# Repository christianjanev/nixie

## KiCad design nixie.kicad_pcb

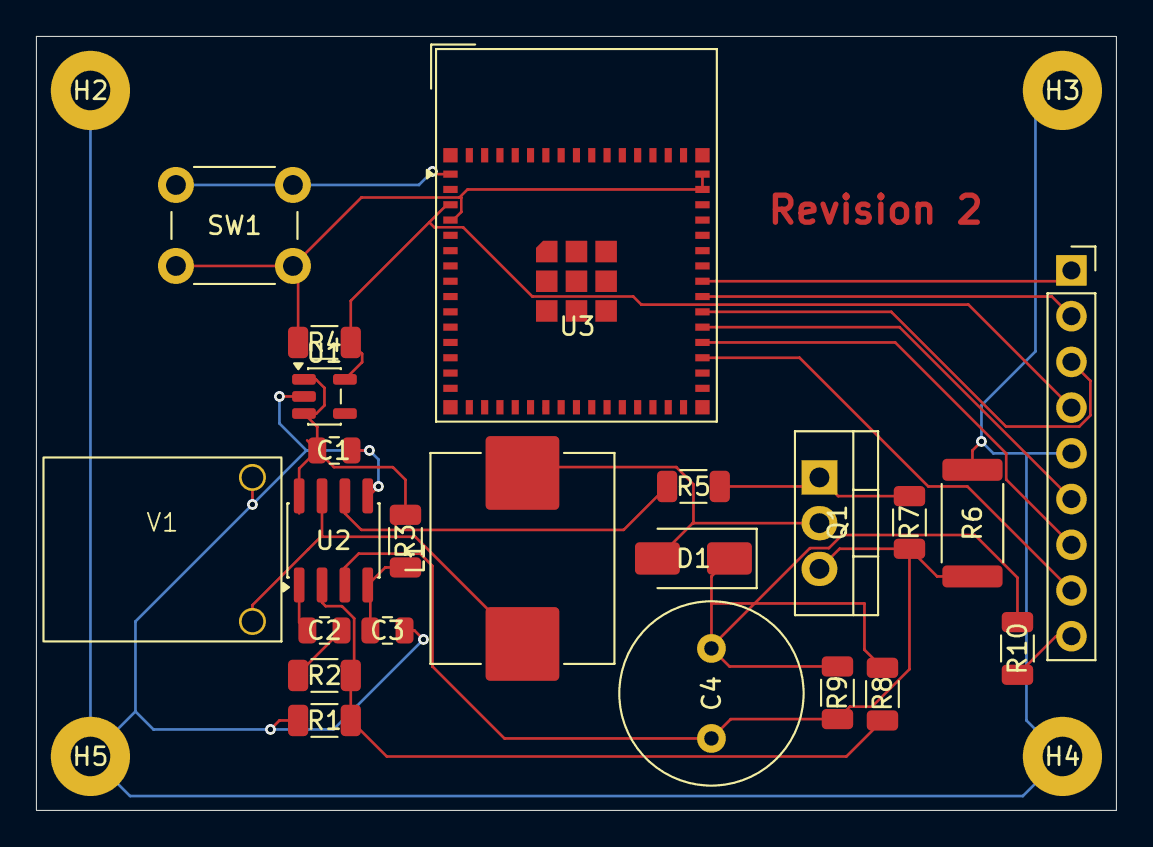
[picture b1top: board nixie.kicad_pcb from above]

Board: 2 copper layers, 60.0 x 43.0 mm, 27 parts (0 on the bottom side), 21 nets.

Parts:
C1: 100nF; C_0805_2012Metric
C2, C3: 1nF; C_0805_2012Metric
C4: 10uF; C_Radial_D10.0mm_H12.5mm_P5.00mm
D1: UF4004; D_SMA
H2, H3, H4, H5: MountingHole_Pad; MountingHole_2.2mm_M2_Pad
J1: Conn_01x09_Pin; PinSocket_1x09_P2.54mm_Vertical
L1: 100uH; L_Sunlord_MWSA1003S
Q1: IRF840A; TO-220-3_Vertical
R1, R3, R4: 10k; R_1206_3216Metric
R2, R10: 20k; R_1206_3216Metric
R5: 10; R_1206_3216Metric
R6: 0.22; R_2512_6332Metric
R7: 51k; R_1206_3216Metric
R8: 680k; R_1206_3216Metric
R9: 220k; R_1206_3216Metric
SW1: DOWNLOAD; SW_PUSH_6mm
U1: AP2112K-3.3; SOT-23-5
U2: UC3843_SOIC8; SOIC-8_3.9x4.9mm_P1.27mm
U3: ESP32-S3-MINI-1; ESP32-S2-MINI-1
V1: 20V; USB C PD Deceiver

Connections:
/power/170V: C4.1, D1.1 (K), R8.2, R9.1, R10.1
/power/CLK_1: J1.3, U3.36 (IO40)
/power/CLK_2: J1.8, U3.33 (IO37)
/power/DATA_IN_1: J1.2, U3.37 (IO41)
/power/DATA_IN_2: J1.7, U3.34 (IO38)
/power/DATA_OUT_1: J1.1, U3.38 (IO42)
/power/DATA_OUT_2: J1.6, U3.35 (IO39)
/power/FB: R1.2, R2.1, R8.1, U2.2 (FB)
/power/VDD: J1.4, R4.1, U1.5 (VOUT), U3.3 (3V3)
/power/VREF: C1.1, R3.1, U1.1 (VIN), U1.3 (EN), U2.8 (VREF)
GND: C1.2, C3.2, H2.1 (1_1), H3.1 (1_1), H4.1 (1_1), H5.1 (1_1), J1.5, R1.1, R6.1, SW1.1, U1.2 (GND), U2.5 (GND), U3.1 (GND), U3.2 (GND), U3.42 (GND), U3.43 (GND), U3.46 (GND), U3.47 (GND), U3.48 (GND), U3.49 (GND), U3.50 (GND), U3.51 (GND), U3.52 (GND), U3.53 (GND), U3.54 (GND), U3.55 (GND), U3.56 (GND), U3.57 (GND), U3.58 (GND), U3.59 (GND), U3.60 (GND), U3.61 (GND), U3.62 (GND), U3.63 (GND), U3.64 (GND), U3.65 (GND), V1.2
unnamed: C2.2, R2.2
unnamed: D1.2 (A), L1.2, Q1.2 (D)
unnamed: J1.9, R10.2
unnamed: Q1.1 (G), R5.2, R7.1
unnamed: C4.2, Q1.3 (S), R6.2, R7.2, R9.2, U2.3 (CS)
unnamed: C2.1, U2.1 (COMP)
unnamed: R5.1, U2.6 (OUT)
unnamed: C3.1, R3.2, U2.4 (RC)
unnamed: R4.2, SW1.2, U3.4 (IO0), U3.44 (IO46), U3.45 (EN)
VCC: L1.1, U2.7 (VCC), V1.1

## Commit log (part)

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2026-06-30 init
